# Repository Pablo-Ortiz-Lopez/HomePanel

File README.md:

# Home Automation Project

Welcome to my Home Automation repository! This custom project has been meticulously crafted to fulfill my specific home automation needs, and I've decided to share it here in case anyone else has similar requirements and is seeking a starting point. 

The project includes a variety of custom hardware, along with an ESPHome + HomeAssistant Docker Compose project. 

Firmware for these devices is powered by ESPHome, enabling seamless over-the-air (OTA) updates to enhance and expand functionality.

## Getting Started

To set up and run the Home Automation Project, follow these steps:

1. **Clone the Repository:** Begin by cloning this repository to your local machine:

   ```
   git clone git@github.com:Pablo-Ortiz-Lopez/HomePanel.git
   cd HomePanel
   ```

2. **Install Docker:** Ensure you have Docker installed on your system, as the project relies on it to manage the services.

3. **Start the Panels:** To launch HomeAssistant + ESPHome, run:

   ```
   ./system start
   ```
> If you don't need ESPHome, you can run this command with the --prod flag.
> 
> Note that stuff may break, contact me if you have any issues starting the Compose project, and I will respond shortly.

4. Access the panels: The control panels can be accessed at
    * HomeAssistant: ```http://localhost```
    * ESPHome: ```http://localhost/esphome```

> It is recommended to setup a CloudFlare proxy to enjoy the benefits of HTTPS and its CDN, for free.

## Custom Hardware

The Home Automation Project features custom hardware components designed to enhance your home automation experience. These components include:

- **Climate Control Unit:** This unit is capable of controlling infrared (IR) based air conditioners. It also features a relay for controlling a heater. Additionally, the climate control unit supports CO2 monitoring using the JST connector, providing insights into air quality in your home.

- **Dimmer:** The dimmer is designed to control the brightness of a lightbulb. Adjust the lighting in any room to create the perfect ambiance for any occasion.

## Firmware and OTA Updates

The firmware for the custom hardware components is powered by ESPHome. This enables seamless over-the-air (OTA) updates, allowing you to improve and expand your devices' functionality without the need for physical updates.

To update the firmware OTA:

1. Make necessary changes to the ESPHome configuration files for your devices.
2. Send the changes to your devices using the ESPHome control panel
   
> Note that the first time you will need to flash ESPHome to your device using Serial. Contact me or check out my blog for more information on this.

> Some devices, namely the LightController, are powered by an Atmega328P microcontroller. Those devices don't use ESPHome, and instead rely on Arduino IDE to flash their firmware via ICSP.
## Additional Information

For more details about the project, you can visit my blog at [ortizma.com](https://ortizma.com). If you have any questions, issues, or suggestions, feel free to contact me directly at [pabloortiz132@gmail.com](mailto:pabloortiz132@gmail.com).

## Contributing

We welcome contributions to the Home Automation Project! If you'd like to improve the project, fix bugs, or add new features, please follow these steps:

1. Fork the repository and create a new branch.
2. Make your changes and improvements.
3. Test your changes thoroughly.
4. Create a pull request detailing your changes and explaining their benefits.

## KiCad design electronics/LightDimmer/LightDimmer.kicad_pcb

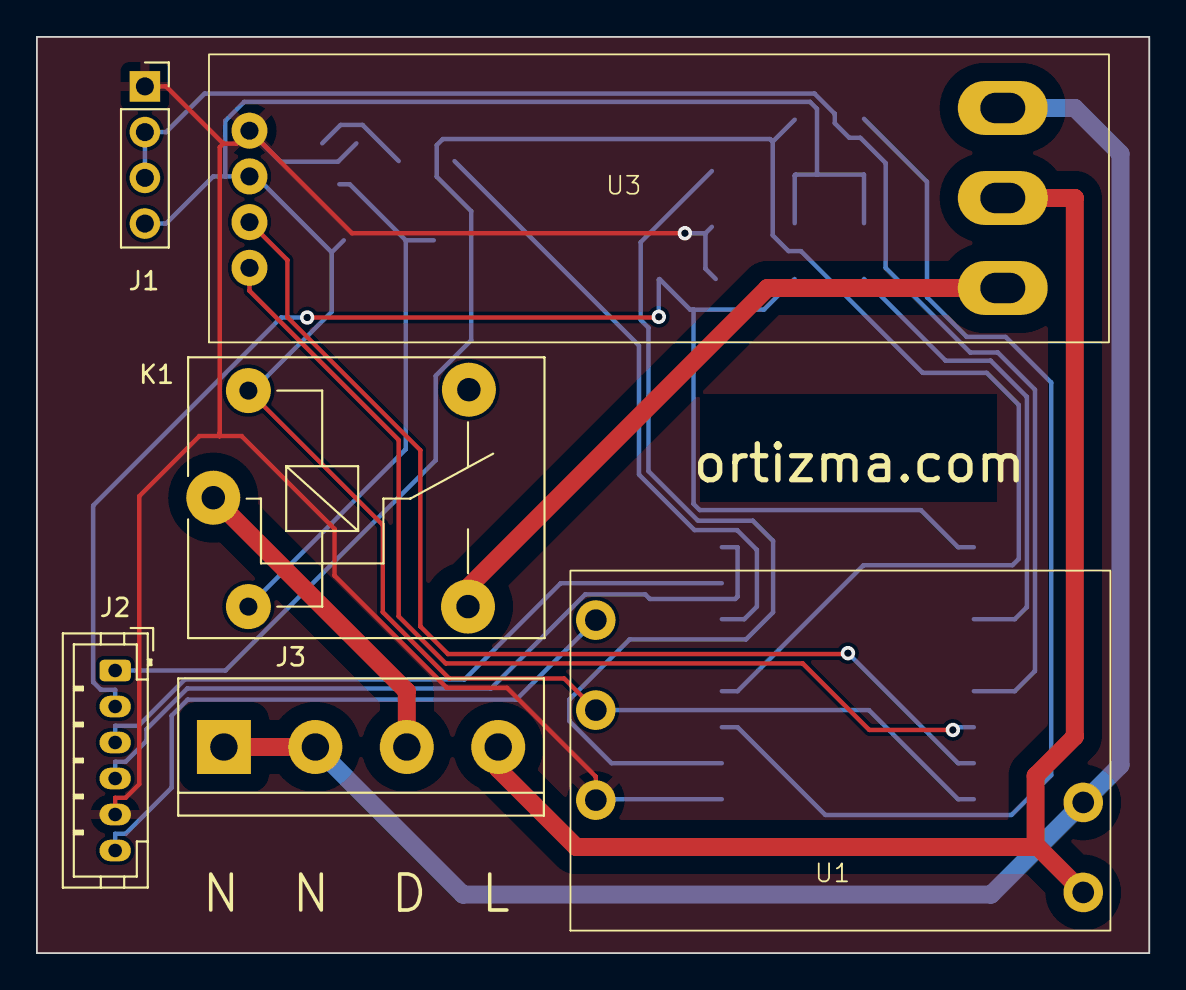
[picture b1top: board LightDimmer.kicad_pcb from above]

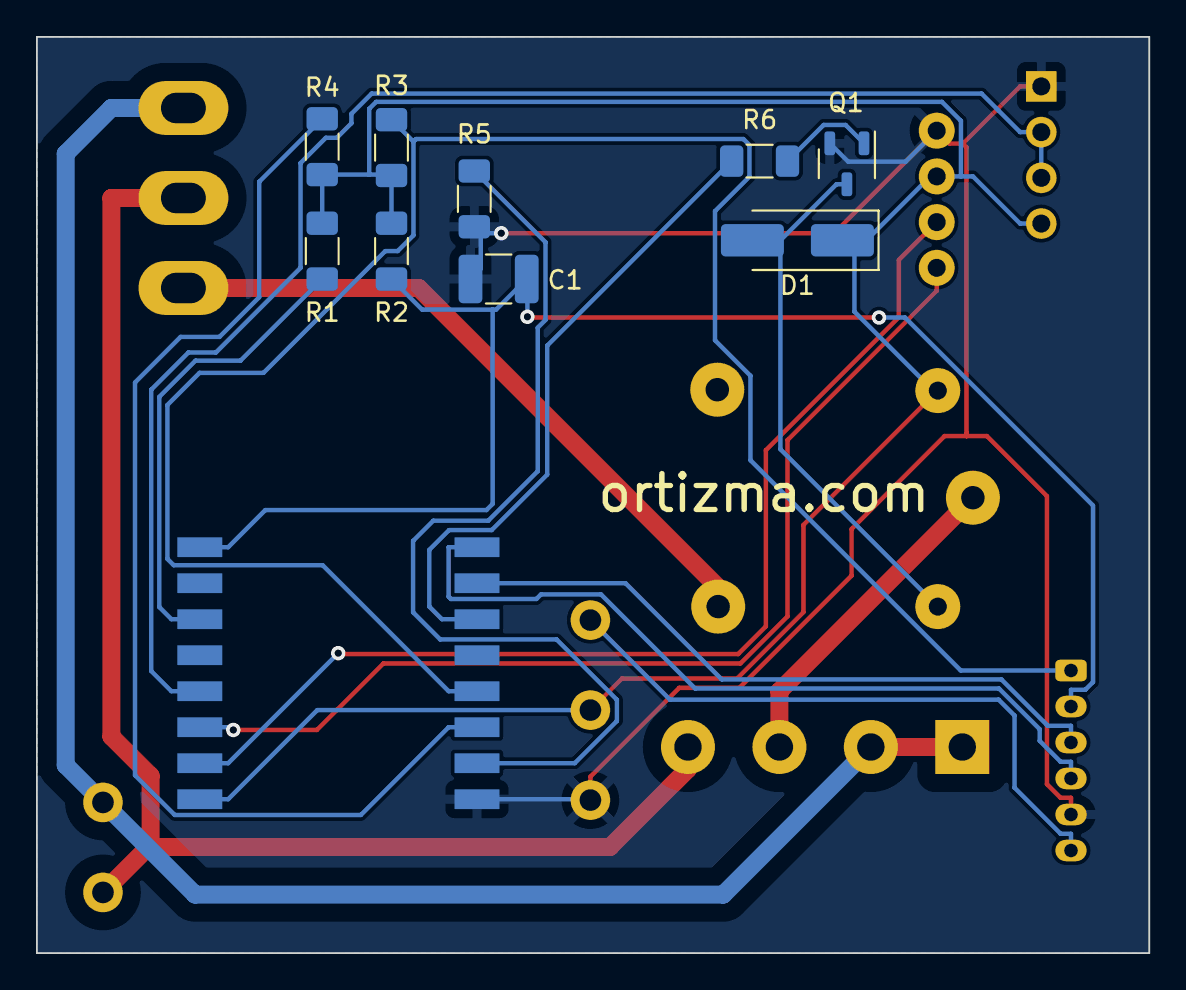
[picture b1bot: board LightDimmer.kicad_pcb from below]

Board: 2 copper layers, 61.8 x 50.9 mm, 16 parts (10 on the bottom side), 20 nets.

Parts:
C1: 100nF; C_1210_3225Metric_Pad1.33x2.70mm_HandSolder
D1: 1N4007; D_SMA_Handsoldering
J1: 433MHz_ASK_Superheterodyne_Receiver; RF Receiver
J2: Serial Terminals; JST_PH_B6B-PH-K_1x06_P2.00mm_Vertical
J3: AC Terminals; Terminal_KF128-4P
K1: SANYOU_SRD_Form_C; Relay_SPDT_SANYOU_SRD_Series_Form_C
Q1: BC547; SOT-23-3-BC
R1, R2, R3, R4, R5: 10K; R_1206_3216Metric_Pad1.30x1.75mm_HandSolder
R6: 1k; R_1206_3216Metric_Pad1.30x1.75mm_HandSolder
U1: 5V07 Transformer; 5V07
U2: ESP-12F; ESP-12E_SMD_Simple
U3: AC_Dimmer_4A; AC Dimmer 4A

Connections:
+3.3V: D1.1 (K), J1.4 (VCC), K1.5, R1.1, R2.1, R3.1, R4.1, U1.4 (3V3), U2.8 (VCC), U3.2 (VCC)
+5V: J2.6, U1.5 (5V)
/EN: R1.2, U2.3 (CH_PD)
/GPIO0: J2.1, R3.2, U2.12 (GPIO0)
/GPIO2: R4.2, U2.11 (GPIO2)
/GPIO5: R6.1, U2.14 (GPIO5)
/GPIO12: U2.6 (GPIO12), U3.4 (DIM)
/GPIO13: U2.7 (GPIO13), U3.3 (ZC)
/GPIO14: J1.2 (DATA), J1.3 (DATA), U2.5 (GPIO14)
/GPIO15: R5.2, U2.10 (GPIO15)
/REST: C1.1, J2.2, R2.2, U2.1 (REST)
/RX: J2.3, U2.15 (RXD)
/TX: J2.4, U2.16 (TXD)
DIMMER_OUT: K1.3, U3.7 (OUT)
GND: C1.2, J1.1 (GND), J2.5, Q1.3 (E), R5.1, U1.3 (GND), U2.9 (GND), U3.1 (GND)
LAMP: J3.3, K1.1
LINE: J3.4, U1.1 (Load), U3.6 (Load)
NEUT: J3.1, J3.2, U1.2 (Neutral), U3.5 (Neutral)
unnamed: D1.2 (A), K1.2, Q1.1 (C)
unnamed: Q1.2 (B), R6.2

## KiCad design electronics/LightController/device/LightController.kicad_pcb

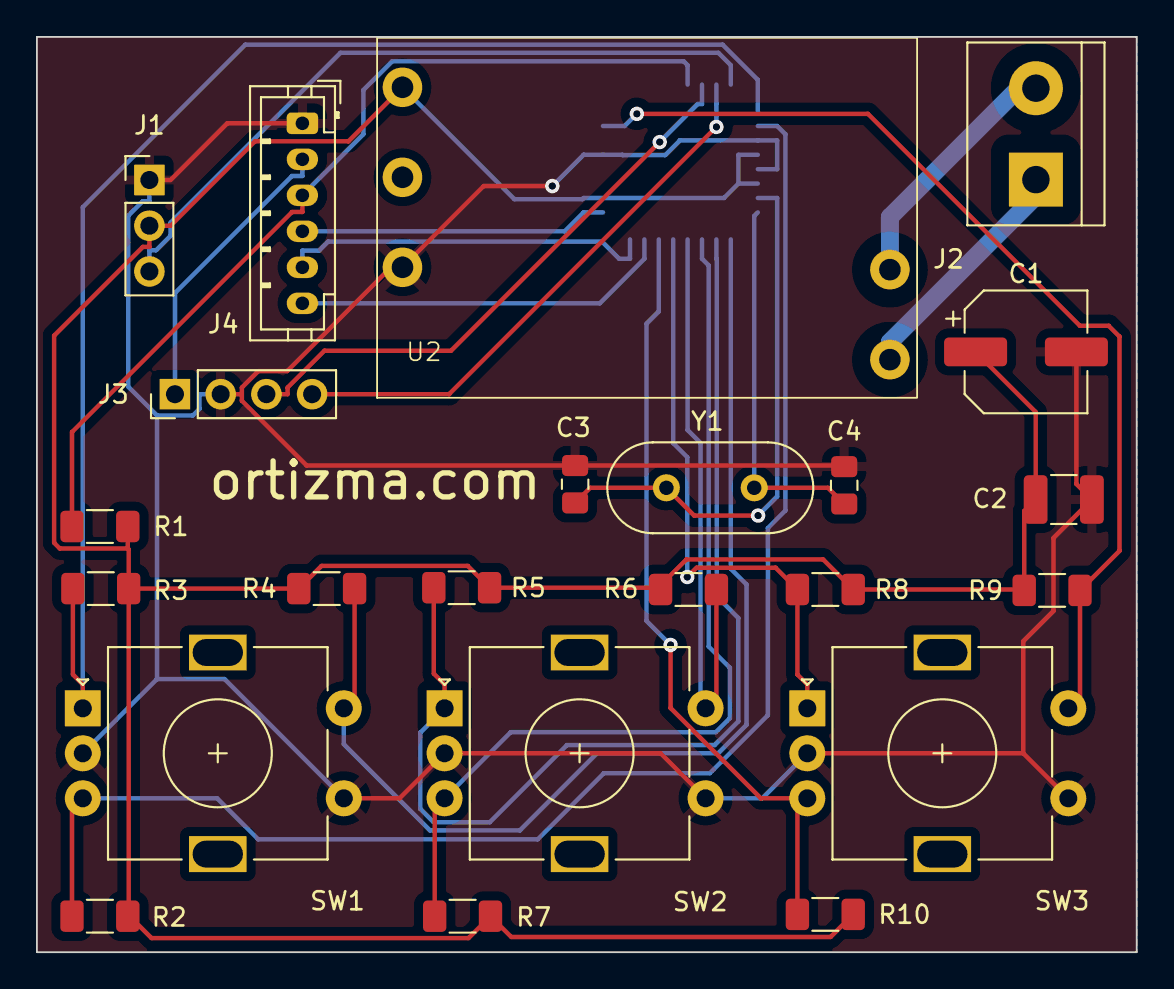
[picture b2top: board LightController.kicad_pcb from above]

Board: 2 copper layers, 61.1 x 50.9 mm, 24 parts (1 on the bottom side), 23 nets.

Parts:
C1: 10uF; CP_Elec_6.3x4.9
C2: 100nF; C_1210_3225Metric_Pad1.33x2.70mm_HandSolder
C3, C4: 22pF; C_0805_2012Metric_Pad1.18x1.45mm_HandSolder
J1: RF_TX; RF ASK Emitter
J2: AC; Terminal_KF128-2P
J3: SERIAL; PinHeader_1x04_P2.54mm_Vertical
J4: ICSP; JST_PH_B6B-PH-K_1x06_P2.00mm_Vertical
R1, R2, R3, R4, R5, R6, R7, R8, R9, R10: 10K; R_1206_3216Metric_Pad1.30x1.75mm_HandSolder
SW1, SW2, SW3: RotaryEncoder_Switch; RotaryEncoder_Alps_EC11E-Switch_Vertical_H20mm
U1: ATMEGA328P-AU; Atmega328p-TQFP
U2: 5V07 Transformer; 5V07
Y1: 16MHz; Crystal_HC49-4H_Vertical

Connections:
+5V: C1.1, C2.1, J1.2 (VCC), R1.2, R2.2, R3.2, R4.1, R5.2, R6.1, R7.2, R8.2, R9.1, R10.2, U1.4 (VCC), U1.6 (VCC), U1.18 (AVCC), U2.5 (5V)
/MISO: J4.5, U1.16 (PB4)
/MOSI: J4.6, U1.15 (PB3)
/PB0: R6.2, SW2.S2, U1.12 (PB0)
/PB1: R8.1, SW3.A, U1.13 (PB1)
/PB2: R10.1, SW3.B, U1.14 (PB2)
/PC0: R9.2, SW3.S2, U1.23 (PC0)
/PD2: J1.3 (DATA), U1.32 (PD2)
/PD3: R3.1, SW1.A, U1.1 (PD3)
/PD4: R2.1, SW1.B, U1.2 (PD4)
/PD5: R4.2, SW1.S2, U1.9 (PD5)
/PD6: R5.1, SW2.A, U1.10 (PD6)
/PD7: R7.1, SW2.B, U1.11 (PD7)
/RESET: J4.3, R1.1, U1.29 (PC6/~RESET)
/RX: J3.4, U1.31 (PD1)
/SCK: J4.4, U1.17 (PB5)
/TX: J3.3, U1.30 (PD0)
GND: C1.2, C2.2, C3.1, C4.1, J1.1 (GND), J3.2, J4.1, SW1.C, SW1.S1, SW2.C, SW2.S1, SW3.C, SW3.S1, U1.3 (GND), U1.5 (GND), U1.21 (GND), U2.3 (GND)
unnamed: J2.2 (AC_N), U2.2 (Neutral)
unnamed: J2.1 (AC_P), U2.1 (Load)
unnamed: C3.2, U1.7 (PB6), Y1.2
unnamed: C4.2, U1.8 (PB7), Y1.1
VCC: J3.1, J4.2

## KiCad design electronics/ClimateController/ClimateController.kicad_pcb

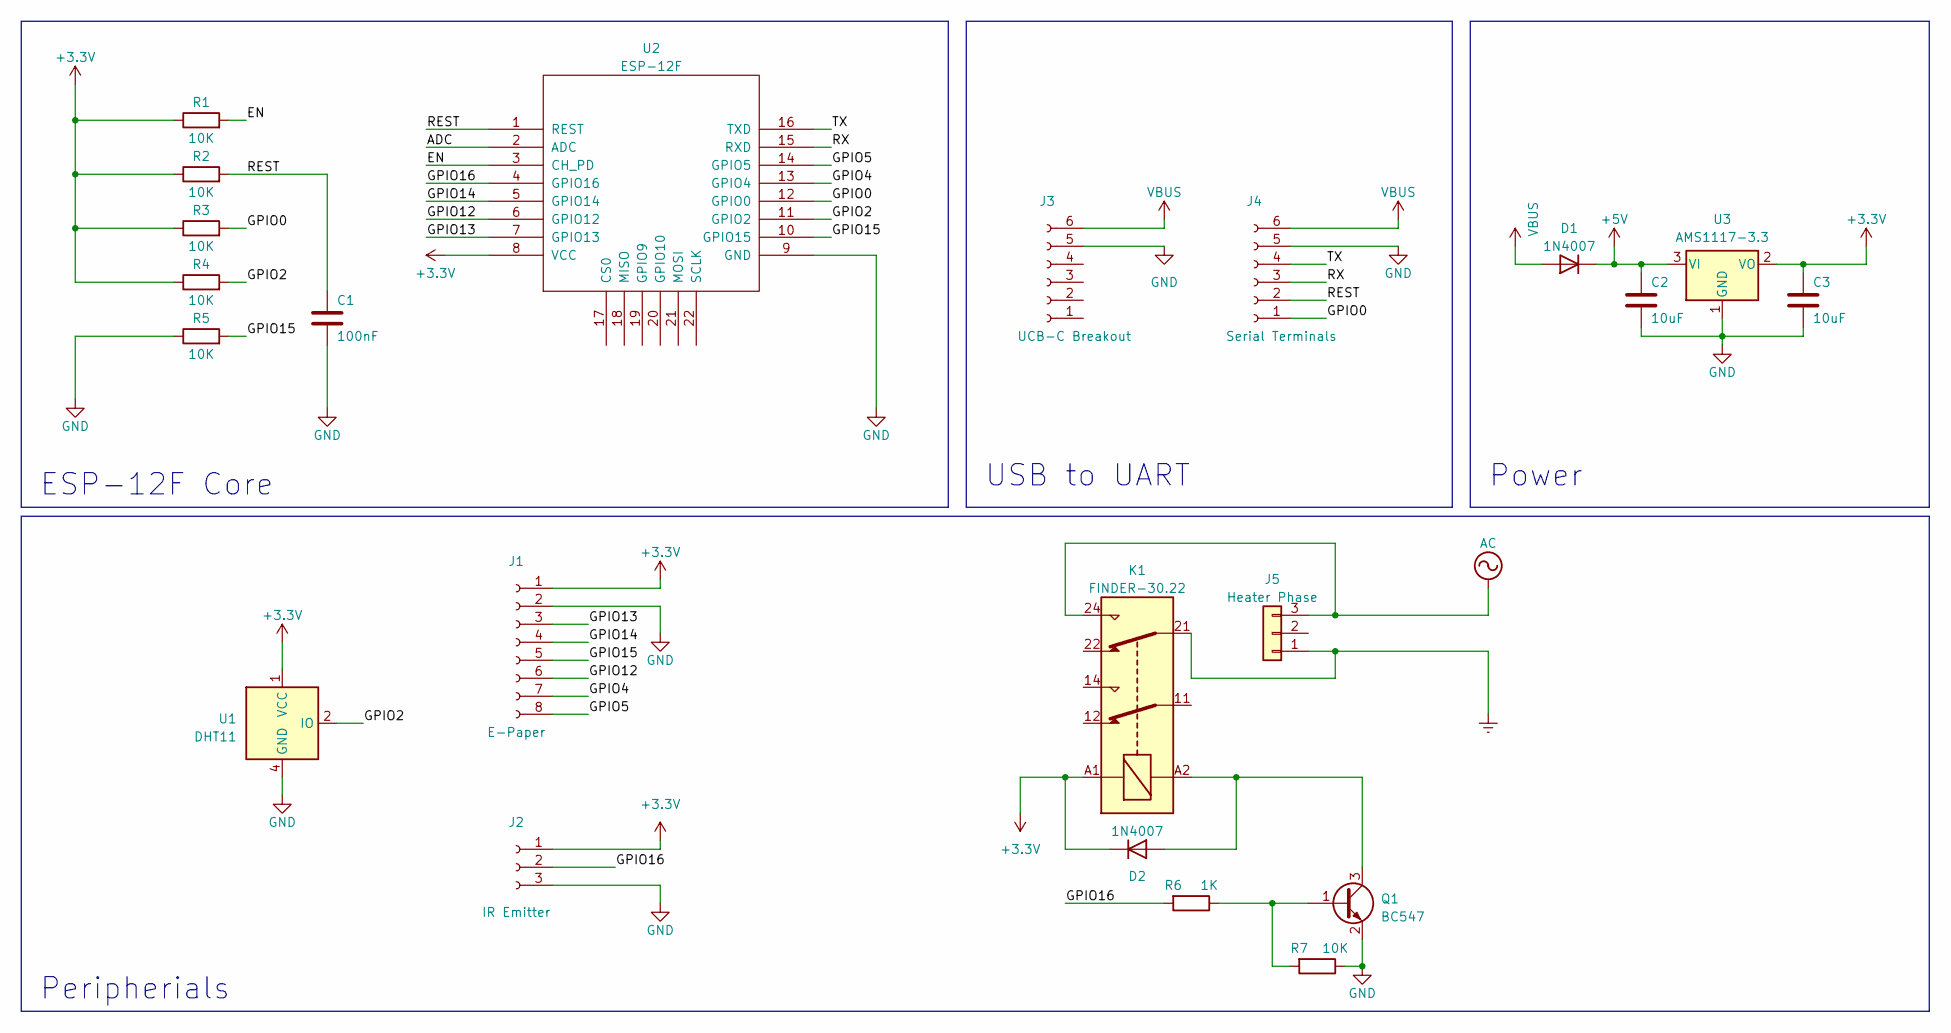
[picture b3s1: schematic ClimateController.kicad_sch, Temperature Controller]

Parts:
C1: 100nF; C_1210_3225Metric_Pad1.33x2.70mm_HandSolder
C2, C3: 10uF; C_1210_3225Metric_Pad1.33x2.70mm_HandSolder
D1, D2: 1N4007; D_SMA_Handsoldering
J1: E-Paper; JST_PH_B8B-PH-K_1x08_P2.00mm_Vertical
J2: IR Emitter; JST_PH_B3B-PH-K_1x03_P2.00mm_Vertical
J3: UCB-C Breakout; USB-C Breakout
J4: Serial Terminals; JST_PH_B6B-PH-K_1x06_P2.00mm_Vertical
J5: Heater Phase; TerminalBlock_bornier-3_P5.08mm
K1: FINDER-30.22; Relay_DPDT_Finder_30.22
Q1: BC547; SOT-23
R1, R2, R3, R4, R5, R7: 10K; R_1206_3216Metric_Pad1.30x1.75mm_HandSolder
R6: 1K; R_1206_3216Metric_Pad1.30x1.75mm_HandSolder
U1: DHT11; Aosong_DHT11_5.5x12.0_P2.54mm
U2: ESP-12F; ESP-12E_SMD
U3: AMS1117-3.3; SOT-223-3_TabPin2

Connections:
+3.3V: C3.1, D2.1 (K), J1.1, J2.1, K1.A1, R1.1, R2.1, R3.1, R4.1, U1.1 (VCC), U2.8 (VCC), U3.2 (VO)
+5V: C2.1, D1.1 (K), U3.3 (VI)
/ADC: U2.2 (ADC)
/EN: R1.2, U2.3 (CH_PD)
/GPIO0: J4.1, R3.2, U2.12 (GPIO0)
/GPIO2: R4.2, U1.2 (IO), U2.11 (GPIO2)
/GPIO4: J1.7, U2.13 (GPIO4)
/GPIO5: J1.8, U2.14 (GPIO5)
/GPIO12: J1.6, U2.6 (GPIO12)
/GPIO13: J1.3, U2.7 (GPIO13)
/GPIO14: J1.4, U2.5 (GPIO14)
/GPIO15: J1.5, R5.2, U2.10 (GPIO15)
/GPIO16: J2.2, R6.2, U2.4 (GPIO16)
/REST: C1.1, J4.2, R2.2, U2.1 (REST)
/RX: J4.3, U2.15 (RXD)
/TX: J4.4, U2.16 (TXD)
AC: J5.3, K1.24
Earth: J5.1, K1.21
GND: C1.2, C2.2, C3.2, J1.2, J2.3, J3.5, J4.5, Q1.2 (E), R5.1, R7.1, U1.4 (GND), U2.9 (GND), U3.1 (GND)
unnamed: D2.2 (A), K1.A2, Q1.3 (C)
unnamed: Q1.1 (B), R6.1, R7.2
VBUS: D1.2 (A), J3.6, J4.6

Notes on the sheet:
Peripherials
USB to UART
Power
ESP-12F Core

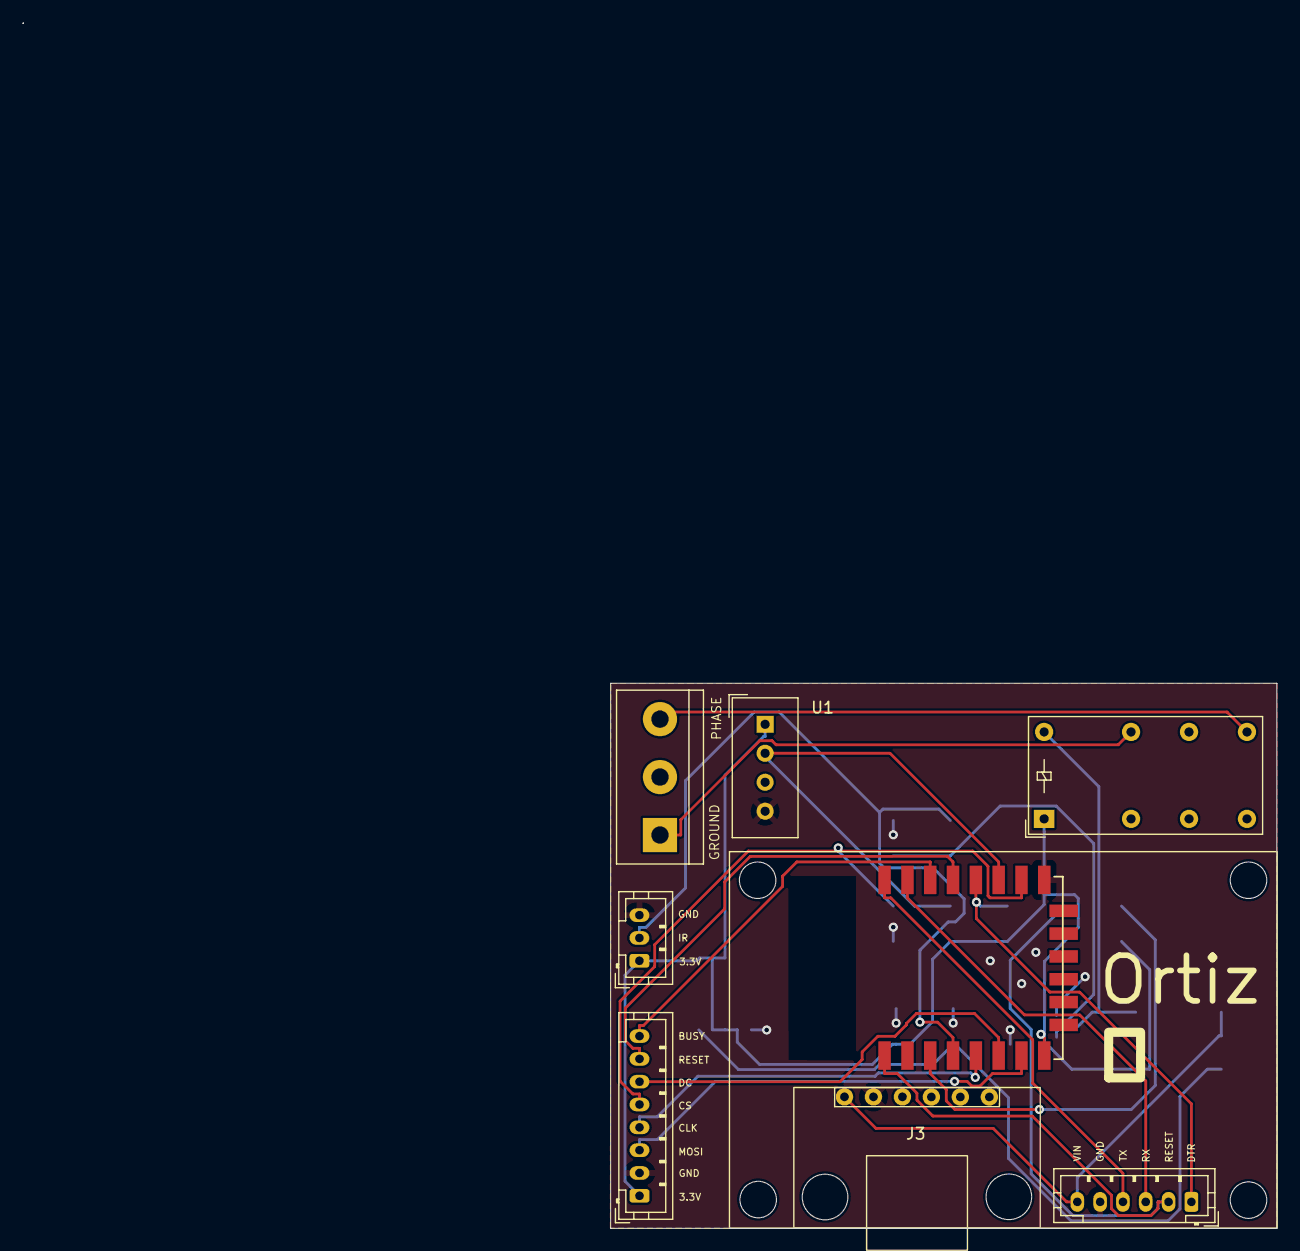
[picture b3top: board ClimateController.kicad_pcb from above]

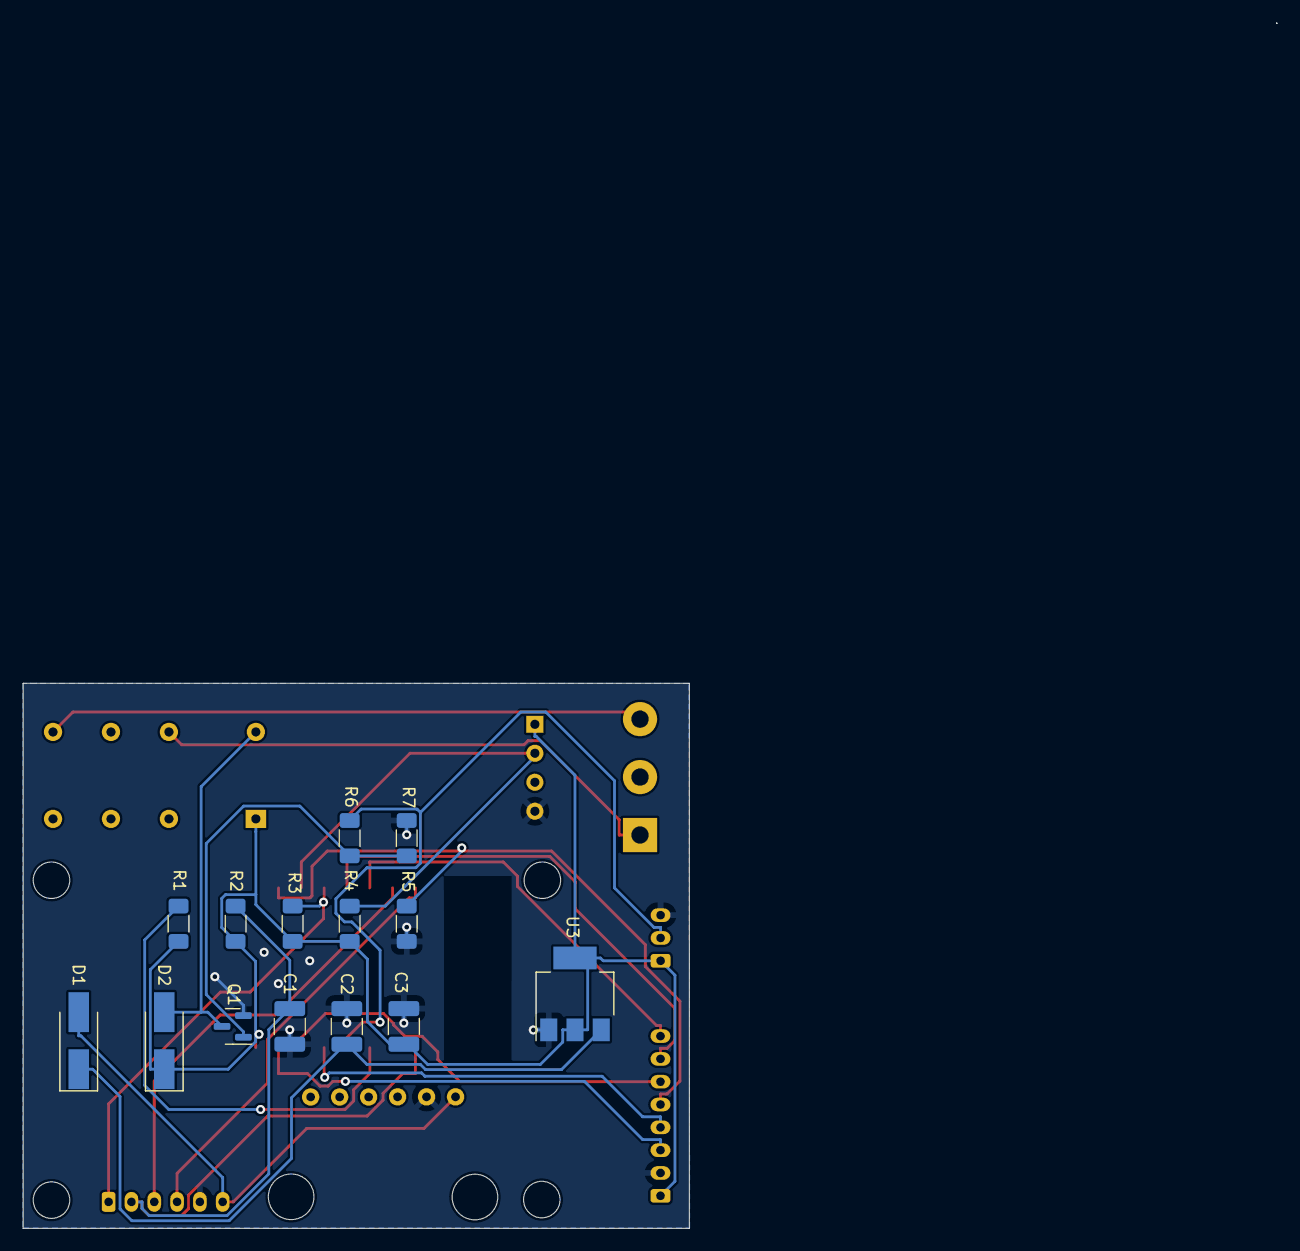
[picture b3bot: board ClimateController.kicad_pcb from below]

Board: 2 copper layers, 109.9 x 105.6 mm, 23 parts (14 on the bottom side), 21 nets.

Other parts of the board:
E-Ink Screen: 1.54in

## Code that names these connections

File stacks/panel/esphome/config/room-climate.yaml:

esphome:
  name: "room-climate"
  friendly_name: "Climatizador del Dormitorio"

esp8266:
  board: esp01_1m

logger:
  level: info
  baud_rate: 0

api:

ota:

wifi:
  ssid: !secret wifi_ssid
  password: !secret wifi_password

  ap:
    ssid: "OrtizMa Room Climate"
    password: !secret mqtt_password

captive_portal:

mqtt:
  broker: !secret mqtt_broker
  username: "pablo"
  password: !secret mqtt_password
  id: mqtt_client

remote_transmitter:
  pin: GPIO16
  carrier_duty_percent: 50%

climate:
  - platform: mitsubishi
    name: "AC"
    id: ac
    on_control:
      - delay: 1s
      - component.update: eink
    sensor: temperature

uart:
  rx_pin: GPIO3
  tx_pin: GPIO1
  baud_rate: 9600
  
sensor:
  - platform: senseair
    co2:
      name: "co2"
      id: co2
    update_interval: 60s
  - platform: dht
    pin: GPIO2
    temperature:
      name: "Temperature"
      id: temperature
      filters:
        - calibrate_linear:
          - 30.1 -> 24.4
          - 30.6 -> 24.8
          - 31.1 -> 25.8
          - 31.4 -> 26
          - 32 -> 26.6
    humidity:
      name: "Humidity"
      id: humidity
      filters:
        offset: 10
          
    update_interval: 15s
    
  - platform: wifi_signal
    name: "WiFi Signal"
    id: wifi_db
    update_interval: 5s

image:
  - file: "images/x.png"
    id: x_image
    resize: 25x25
    type: TRANSPARENT_IMAGE
  - file: "images/fire.png"
    id: fire_image
    resize: 70x70
    type: TRANSPARENT_IMAGE
  - file: "images/snowflake.png"
    id: snowflake_image
    resize: 55x55
    type: TRANSPARENT_IMAGE
  - file: "images/power.png"
    id: power_image
    resize: 90x90
    type: TRANSPARENT_IMAGE
  - file: "images/plug.png"
    id: plug_image
    resize: 25x25
    type: TRANSPARENT_IMAGE
    
font:
  - file: "gfonts://Roboto"
    id: roboto18
    size: 18
  - file: "gfonts://Roboto"
    id: roboto
    size: 25
  - file: "gfonts://Roboto"
    id: roboto_mid
    size: 45
  - file: "gfonts://Roboto"
    id: roboto_big
    size: 60

time:
  - id: reloj
    platform: sntp
    timezone: Europe/Madrid

spi:
  clk_pin: GPIO14
  mosi_pin: GPIO13

display:
  - platform: waveshare_epaper
    id: eink
    cs_pin: GPIO15
    dc_pin: GPIO12
    reset_pin: GPIO4
    busy_pin: GPIO5
    model: 1.54inv2
    rotation: 270
    full_update_every: 1
    update_interval: 60s
    reset_duration: 200ms
    lambda: |-
      it.image(5, 8, id(plug_image));
      
      auto time = id(reloj).now();
      
      if(time.is_valid()){
        it.printf(70,5,id(roboto), TextAlign::TOP_LEFT, "%02d:%02d", time.hour, time.minute);
      }

      if(id(wifi_db).has_state()){ // WIFI OK
        if (!id(mqtt_client)->is_connected()) { // MQTT KO
          it.printf(175, 5, id(roboto), TextAlign::TOP_LEFT , "!");
        }else{ // WIFI & MQTT OK
          it.filled_rectangle(150, 25, 8, 5); // 1 Bar

          if(id(wifi_db).has_state() && id(wifi_db).state > -90){ // 2 Bars
            it.filled_rectangle(160, 20, 8, 10);
          }else{
            it.rectangle(160, 20, 8, 10);
          }

          if(id(wifi_db).has_state() && id(wifi_db).state > -80){ // 3 Bars
            it.filled_rectangle(170, 15, 8, 15);
          }else{
            it.rectangle(170, 15, 8, 15);
          }

          if(id(wifi_db).has_state() && id(wifi_db).state > -70){ // 4 Bars
            it.filled_rectangle(180, 10, 8, 20);
          }else{
            it.rectangle(180, 10, 8, 20);
          }

          if(id(wifi_db).has_state() && id(wifi_db).state > -60){ // 5 Bars
            it.filled_rectangle(190, 5, 8, 25);
          }else{
            it.rectangle(190, 5, 8, 25);
          }
        }
      }else{ // WIFI KO
        it.image(175, 5, id(x_image));
      }
      
      if (id(humidity).has_state()) { // Humidity
        it.printf(5, 65, id(roboto), TextAlign::BOTTOM_LEFT , "%.1f%%", id(humidity).state);
      }else{
        it.printf(5, 65, id(roboto), TextAlign::BOTTOM_LEFT , "--.-%%");
      }
      it.printf(5, 88, id(roboto18), TextAlign::BOTTOM_LEFT , "Humedad");

      if (id(co2).has_state()) { //CO2
        if(id(co2).state > 1500){
          it.printf(118, 62, id(roboto18), TextAlign::BOTTOM_LEFT , "!");
          it.line(110, 60, 120, 40);
          it.line(120, 40, 130, 60);
          it.line(130, 60, 110, 60);
        }
        it.printf(195, 65, id(roboto), TextAlign::BOTTOM_RIGHT , "%.0f", id(co2).state);
      }else{
        it.printf(195, 65, id(roboto), TextAlign::BOTTOM_RIGHT , "- - -");
      }
      it.printf(195, 88, id(roboto18), TextAlign::BOTTOM_RIGHT , "ppm (CO2)");
      
      if (id(temperature).has_state()) { // Temperature
        it.printf(195, 138, id(roboto_mid), TextAlign::BOTTOM_RIGHT , "%.1f°", id(temperature).state);
      }else{
        it.printf(195, 138, id(roboto_mid), TextAlign::BOTTOM_RIGHT , "--.-°");
      }

      if(id(ac).mode != 0){
        it.printf(195, 200, id(roboto_big), TextAlign::BOTTOM_RIGHT , "%.1f°", id(ac).target_temperature);
        if(id(ac).mode == 2){
        it.image(0, 130, id(snowflake_image));
        }else if(id(ac).mode == 3){
          it.image(0, 125, id(fire_image));
        }
      }else{
        it.image(0, 100, id(power_image));
        it.printf(195, 200, id(roboto_big), TextAlign::BOTTOM_RIGHT , "OFF");
      }

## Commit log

2023-08-21 Add config for Oriol
2023-08-21 RF Dimmer prototype is working
2023-08-21 Implement RCSwitch based protocol
2023-08-21 Start designing PCB for Controller
2023-08-21 Print code in hexadecimal
2023-08-21 Button is working
2023-08-21 Button is working in emitter
2023-08-22 Arrange folder
2023-08-23 Rename KiCad files
2023-08-23 Add RF receiver in Dimmer
2023-08-24 Improve file naming & Design V2 Dimmer iteration & Lay components in PCB
2023-08-24 Finish LightDimmer PCB Design V2
2023-08-24 Arrance components in LightController PCB
2023-08-25 Finish LightController PCB design with 3 switches
2023-08-26 Improved the designs of LightController & LightDimmer PCBs
2023-08-26 Add clarification in Readme
2023-08-26 Small adjustments before JLC order
2023-09-12 Change firmware to PlatformIO
2023-10-10 Try to implement multi-encoder controller (not working)
2023-10-10 Fix docker compose
2023-10-10 Fix subnet
2023-10-10 <fix>[HomeAssistant] now accepts 192.168.0.0 networks requests
2023-10-22 Move devices to separate repositories
2023-10-23 Add duck devices to ESPHome
2023-10-24 Update ClimateController index
2023-10-24 Add windows YML file to be able to run ESPHome in windows hosts
2023-10-24 Prevent CLI from using windows compose file
2023-10-24 Remove homekit from webserver
2023-10-24 Added windows case to Bash entrypoint
2023-10-24 Avoid fallthrough in bash script & Rename Pato Marc
2023-10-26 Murdered all devices except my duck ^^
2024-01-27 Use average temperature for thermostat
2024-01-30 Directly call docker compose because it suits this project's needs better
2024-02-07 Only start NGINX in DEV mode where it is needed
2024-02-07 Update HA & add healthcheck
